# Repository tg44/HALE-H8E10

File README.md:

# HALE H8E10

**H**all ×**8**, **E**ncoder ×**10**. An open-source USB-MIDI pad controller with hall-effect (analog) keys, ten
push-encoders, a small colour display and per-key RGB, built around an
ESP32-S3 so it can also do BLE-MIDI and a Wi-Fi settings page.

Think "LPD8-sized, with velocity and aftertouch that actually come from the
key, and an Ableton/DJ mode flip for the knobs."

> Inspired by the Akai Professional LPD8 and MPK mini. This project is not
> affiliated with or endorsed by Akai; those names are used only to describe
> the layout it takes after.

## What it is

- 8 hall-effect keys (Gateron KS-20 magnetic switches, DRV5055A3 sensors) with
  per-key velocity, aftertouch and rapid-trigger style actuation
- 10 detented push-encoders in two rows; a row reads `[browse][hi][mid][lo][mix]`
  in "DJ" mode and ten macro knobs in "Ableton" mode
- 2.79" 428×142 bar display (NV3007, SPI) in a strip above the keys
- 18 reverse-mount RGB LEDs (SK6812MINI-EA), one per key and one per encoder; no separate status LEDs (the display and ENC1's LED cover status)
- Seeed XIAO ESP32S3 Plus: class-compliant USB-MIDI, BLE-MIDI, Wi-Fi web UI
- Powered from the XIAO's USB-C; no external supply

## Name

The model code follows the Intech/Akai habit of letters-and-counts: `H8E10` is
8 hall-effect keys and 10 encoders, so a 32-key sibling would be `H16E16` and
a fader version `H8E10F4`. **HALE** is the family name (HALl Encoder; also
"hale" as in healthy and strong). Yes, H8 reads as "hate". We're fine with it (or at least I don't _hate_ it, I think its F8 so we can make fun jokes (or F1?)).

## Status

Nothing is ordered yet. The H8E10 schematic and board are drawn and
routed; the case is modelled alongside. Before ordering it, a mini test
board, H4E2 (4 keys, 2 encoders, the same display), checks the footprints
and the hall-sensor circuit. v0 will be a single hand-soldered board. See [docs/plan.md](docs/plan.md) for the order of work and
[docs/decisions.md](docs/decisions.md) for why things are the way they are.

## AI-assisted, not AI-generated

I'm building this to learn electronics, and I use an AI assistant (Claude)
while doing it — as a tutor and a second pair of eyes, not as the designer.
It explains things, suggests parts and helps keep these docs in order. The
schematic and layout are drawn by me in KiCad, every part choice is checked
against its datasheet, and the reasoning is written down in
[docs/decisions.md](docs/decisions.md) so that it can be checked by someone
who knows better.

That's also an invitation: I'm new to this, so if something here is wrong
or naive, an issue saying so is very welcome.

## Repository layout

```
docs/           design notes, decisions, BOM, assembly notes
hardware/H8E10/ KiCad 10 project (schematic, PCB)
hardware/H4E2/  KiCad 10 project of the mini test board
hardware/libs/  project-local symbols, footprints, 3D models
firmware/       Arduino (PlatformIO) firmware for the XIAO ESP32S3
case/           case and plate models (FluidCAD): lib/, h8e10/, mini/
```

## Docs

- [docs/plan.md](docs/plan.md) — order of work: board, case and firmware
  tracks
- [docs/decisions.md](docs/decisions.md) — architecture decisions and the
  reasoning behind them
- [docs/bom.md](docs/bom.md) — bill of materials with LCSC numbers and sources
- [docs/pinout.md](docs/pinout.md) — MCU pin budget and bus assignments
- [docs/layout-references.md](docs/layout-references.md) — key/knob spacing
  and 3D-print thickness references behind `case/lib/parts.js`
- [docs/pcb-notes.md](docs/pcb-notes.md) — layout and assembly rules
- [display candidates](hardware/libs/datasheets/display/candidates.md) — the 2.79" bar (chosen, D16) vs. the
  1.54" ([display.md](hardware/libs/datasheets/display/1.54/display.md)) and others, mechanical

## License

Hardware: CERN-OHL-P-2.0 ([LICENSE-HARDWARE.md](LICENSE-HARDWARE.md)).
Firmware: MIT ([LICENSE](LICENSE)).

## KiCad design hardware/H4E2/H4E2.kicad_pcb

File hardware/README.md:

# Hardware

- `H8E10/` — KiCad 10 project `HALE-H8E10.kicad_pro`, the full board
- `H4E2/` — KiCad 10 project `H4E2.kicad_pro`, the mini test board (D26);
  started as a copy of the H8E10 project
- `libs/` — project-local symbols (`HALE-git.kicad_sym`), footprints
  (`HALE-git.pretty/`), 3D models (`3dmodels/`, sources in its SOURCES.md), datasheets
  (`datasheets/<group>/`: adc, display, encoder, hall, io-expander, led,
  mcu, power, switch). Every
  part used on the board gets all of them here, so the project opens
  without any globally installed library.

Where parts come from:

- LCSC parts: `easyeda2kicad --full --lcsc_id=Cxxxx` gives symbol, footprint
  and 3D model in one go. Check the result against the datasheet.
- switches: marbastlib, ai03 MX_V2
- XIAO: Seeed OPL_Kicad_Library
- display: Cuprum77/kicad-displays

Copy what is used into `libs/`; don't reference the upstream libraries.

See `docs/pcb-notes.md` before placing anything, and `docs/plan.md` for the
order parts are collected and placed in.

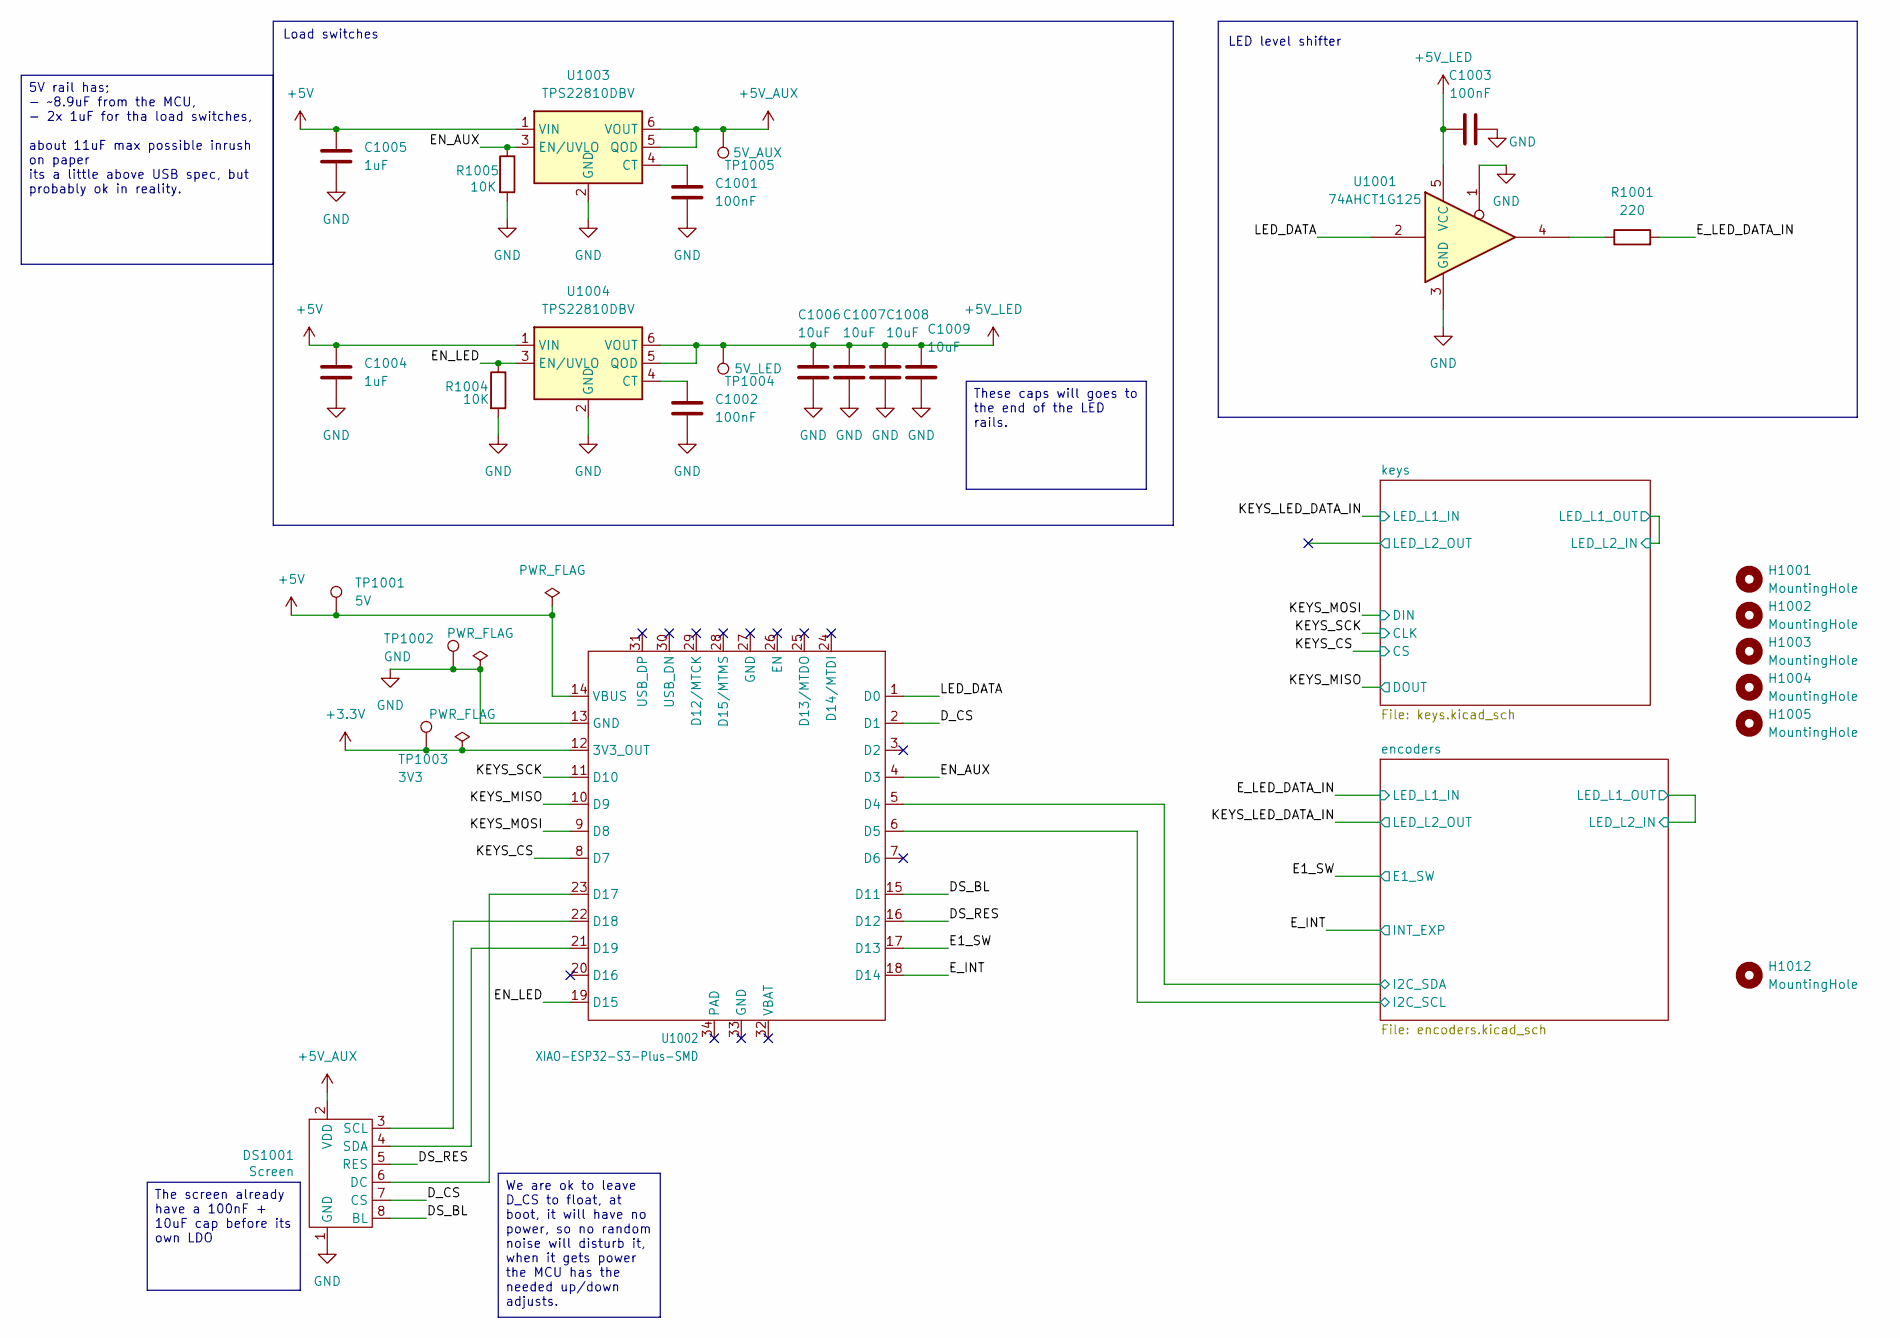
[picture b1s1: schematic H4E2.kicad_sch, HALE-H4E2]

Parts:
C1001, C1002, C1003: 100nF; C_0603_1608Metric_Pad1.08x0.95mm_HandSolder; LCSC C14663
C1004, C1005: 1uF; C_0603_1608Metric_Pad1.08x0.95mm_HandSolder; LCSC C15849
C1006, C1007, C1008, C1009: 10uF; C_0805_2012Metric_Pad1.18x1.45mm_HandSolder; LCSC C15850
DS1001: Screen; Display_2.79_NV3007
H1001, H1002, H1003, H1004, H1005, H1012: MountingHole; MountingHole_2.2mm_M2
R1001: 220; R_0603_1608Metric_Pad0.98x0.95mm_HandSolder; LCSC C22962
R1004, R1005: 10K; R_0603_1608Metric_Pad0.98x0.95mm_HandSolder; LCSC C25804
TP1001: 5V; TestPoint_Pad_D2.0mm
TP1002: GND; TestPoint_Pad_D2.0mm
TP1003: 3V3; TestPoint_Pad_D2.0mm
TP1004: 5V_LED; TestPoint_Pad_D2.0mm
TP1005: 5V_AUX; TestPoint_Pad_D2.0mm
U1001: 74AHCT1G125; SOT-23-5; LCSC C7484
U1002: XIAO-ESP32-S3-Plus-SMD; LCSC C47997983
U1003, U1004: TPS22810DBV; SOT-23-6; LCSC C205990

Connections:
+3.3V: TP1003.1 (1_1), U1002.12 (3V3_OUT); also elsewhere on the board
+5V: C1004.1, C1005.1, TP1001.1 (1_1), U1002.14 (VBUS), U1003.1 (VIN), U1004.1 (VIN)
+5V_AUX: DS1001.2 (VDD), TP1005.1 (1_1), U1003.5 (QOD), U1003.6 (VOUT); also elsewhere on the board
+5V_LED: C1003.2, C1006.1, C1007.1, C1008.1, C1009.1, TP1004.1 (1_1), U1001.5 (VCC), U1004.5 (QOD), U1004.6 (VOUT); also elsewhere on the board
/DS_BL: DS1001.8 (BL), U1002.15 (D11)
/DS_RES: DS1001.5 (RES), U1002.16 (D12)
/D_CS: DS1001.7 (CS), U1002.2 (D1)
/E1_SW: U1002.17 (D13); also elsewhere on the board
/EN_AUX: R1005.1, U1002.4 (D3), U1003.3 (EN/UVLO)
/EN_LED: R1004.1, U1002.19 (D15), U1004.3 (EN/UVLO)
/E_INT: U1002.18 (D14); also elsewhere on the board
/E_LED_DATA_IN: R1001.2; also elsewhere on the board
/KEYS_CS: U1002.8 (D7); also elsewhere on the board
/KEYS_MISO: U1002.10 (D9); also elsewhere on the board
/KEYS_MOSI: U1002.9 (D8); also elsewhere on the board
/KEYS_SCK: U1002.11 (D10); also elsewhere on the board
/LED_DATA: U1001.2, U1002.1 (D0)
/encoders/I2C_SCL: U1002.6 (D5); also elsewhere on the board
/encoders/I2C_SDA: U1002.5 (D4); also elsewhere on the board
GND: C1001.2, C1002.2, C1003.1, C1004.2, C1005.2, C1006.2, C1007.2, C1008.2, C1009.2, DS1001.1 (GND), R1004.2, R1005.2, TP1002.1 (1_1), U1001.1, U1001.3 (GND), U1002.13 (GND), U1003.2 (GND), U1004.2 (GND); also elsewhere on the board
unnamed: DS1001.6 (DC), U1002.23 (D17)
unnamed: DS1001.3 (SCL), U1002.22 (D18)
unnamed: DS1001.4 (SDA), U1002.21 (D19)
unnamed: R1001.1, U1001.4
unnamed: C1001.1, U1003.4 (CT)
unnamed: C1002.1, U1004.4 (CT)

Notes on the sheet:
The screen already have a 100nF + 10uF cap before its own LDO
We are ok to leave D_CS to float, at boot, it will have no power, so no random noise will disturb it, when it gets power the MCU has the needed up/down adjusts.
These caps will goes to the end of the LED rails.
5V rail has; - ~8.9uF from the MCU, - 2x 1uF for tha load switches, about 11uF max possible inrush on paper its a little above USB spec, but probably ok in reality.
Load switches
LED level shifter

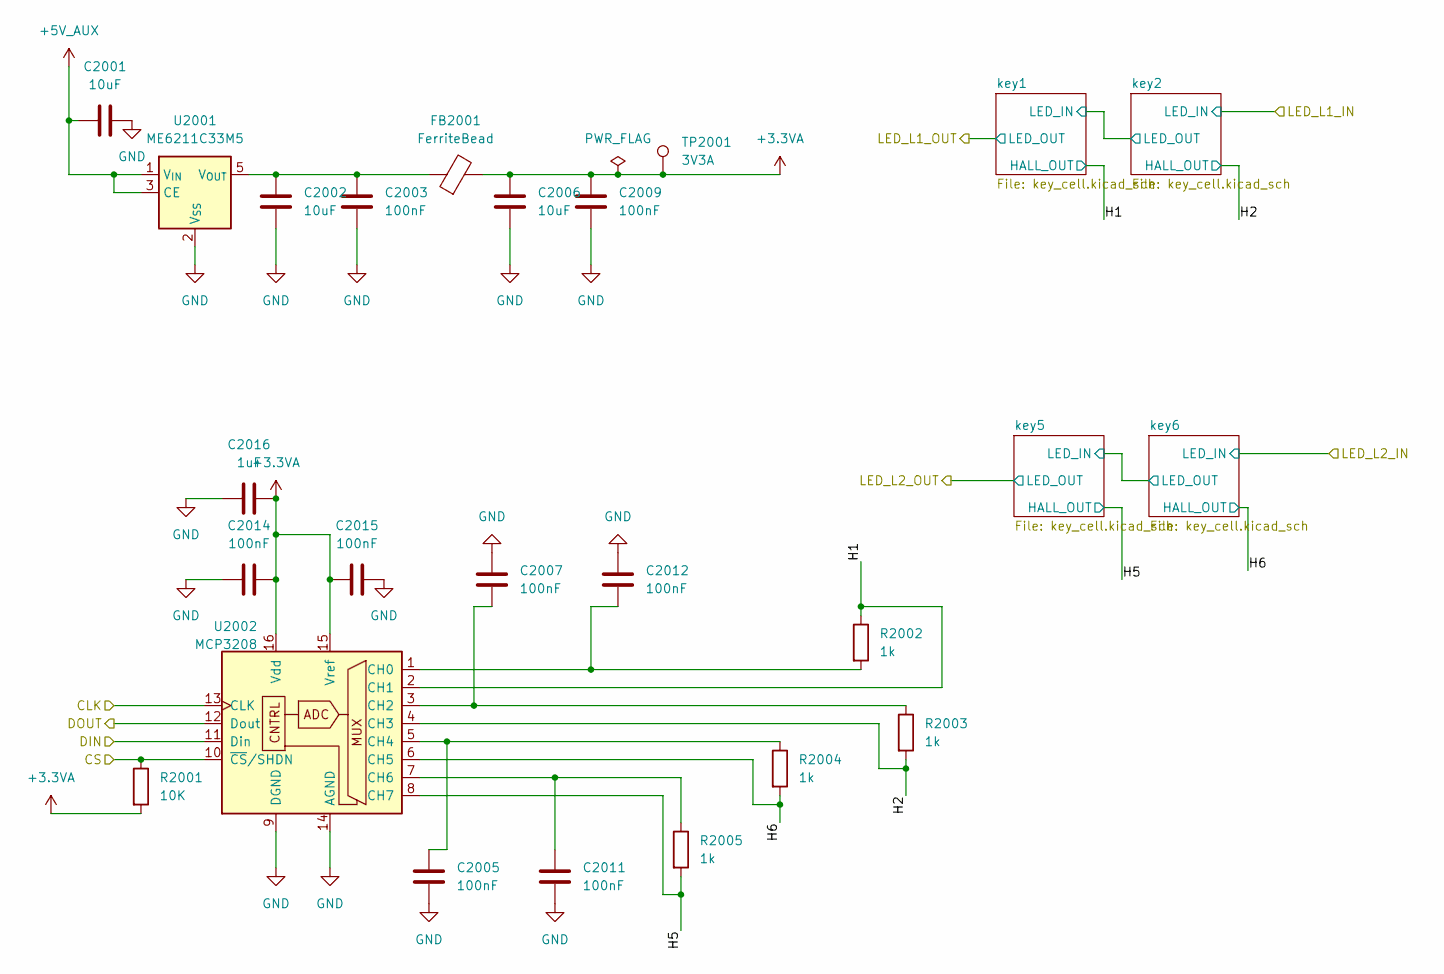
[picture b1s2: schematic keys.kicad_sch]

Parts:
C2001, C2002, C2006: 10uF; C_0805_2012Metric_Pad1.18x1.45mm_HandSolder; LCSC C15850
C2003, C2005, C2007, C2009, C2011, C2012, C2014, C2015: 100nF; C_0603_1608Metric_Pad1.08x0.95mm_HandSolder; LCSC C14663
C2016: 1uF; C_0603_1608Metric_Pad1.08x0.95mm_HandSolder; LCSC C15849
FB2001: FerriteBead; L_0603_1608Metric_Pad1.05x0.95mm_HandSolder; LCSC C1002
R2001: 10K; R_0603_1608Metric_Pad0.98x0.95mm_HandSolder; LCSC C25804
R2002, R2003, R2004, R2005: 1k; R_0603_1608Metric_Pad0.98x0.95mm_HandSolder
TP2001: 3V3A; TestPoint_Pad_D2.0mm
U2001: ME6211C33M5; SOT-23-5; LCSC C82942
U2002: MCP3208; SOIC-16_3.9x9.9mm_P1.27mm; LCSC C626764

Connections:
+3.3VA: C2006.1, C2009.1, C2014.1, C2015.2, C2016.1, FB2001.2, R2001.2, TP2001.1 (1_1), U2002.15 (Vref), U2002.16 (Vdd); also elsewhere on the board
+5V_AUX: C2001.1, U2001.1 (V_{IN}), U2001.3 (CE); also elsewhere on the board
/KEYS_CS: R2001.1, U2002.10 (~CS/SHDN); also elsewhere on the board
/KEYS_MISO: U2002.12 (Dout); also elsewhere on the board
/KEYS_MOSI: U2002.11 (Din); also elsewhere on the board
/KEYS_SCK: U2002.13 (CLK); also elsewhere on the board
/keys/H1: R2002.1, U2002.2 (CH1); also elsewhere on the board
/keys/H2: R2003.2, U2002.4 (CH3); also elsewhere on the board
/keys/H5: R2005.2, U2002.8 (CH7); also elsewhere on the board
/keys/H6: R2004.2, U2002.6 (CH5); also elsewhere on the board
GND: C2001.2, C2002.2, C2003.2, C2005.1, C2006.2, C2007.2, C2009.2, C2011.1, C2012.2, C2014.2, C2015.1, C2016.2, U2001.2 (V_{SS}), U2002.9 (DGND), U2002.14 (AGND); also elsewhere on the board
unnamed: C2002.1, C2003.1, FB2001.1, U2001.5 (V_{OUT})
unnamed: C2012.1, R2002.2, U2002.1 (CH0)
unnamed: C2007.1, R2003.1, U2002.3 (CH2)
unnamed: C2005.2, R2004.1, U2002.5 (CH4)
unnamed: C2011.2, R2005.1, U2002.7 (CH6)

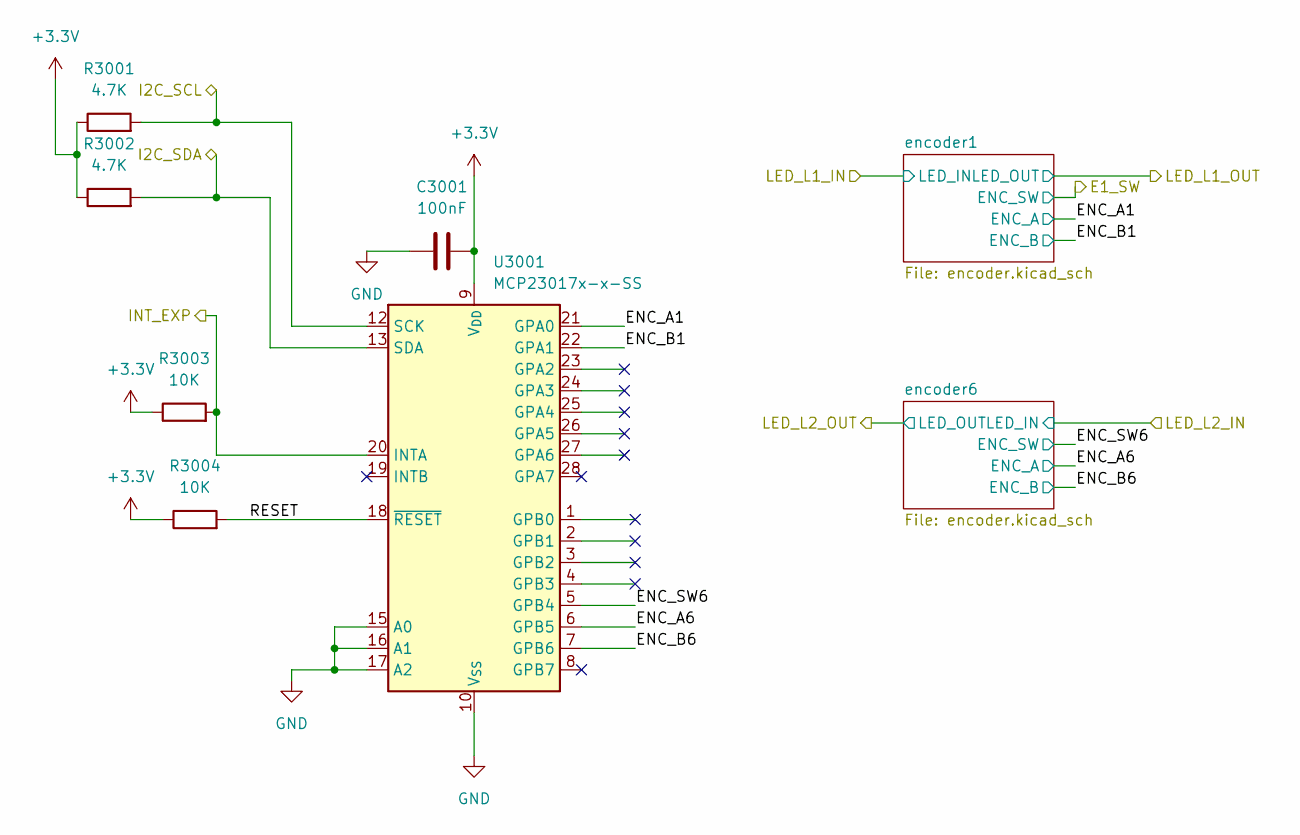
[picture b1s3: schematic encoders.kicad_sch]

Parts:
C3001: 100nF; C_0603_1608Metric_Pad1.08x0.95mm_HandSolder; LCSC C14663
R3001, R3002: 4.7K; R_0603_1608Metric_Pad0.98x0.95mm_HandSolder; LCSC C23162
R3003, R3004: 10K; R_0603_1608Metric_Pad0.98x0.95mm_HandSolder; LCSC C25804
U3001: MCP23017x-x-SS; SSOP-28_5.3x10.2mm_P0.65mm; LCSC C506653

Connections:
+3.3V: C3001.2, R3001.1, R3002.1, R3003.1, R3004.1, U3001.9 (V_{DD}); also elsewhere on the board
/E_INT: R3003.2, U3001.20 (INTA); also elsewhere on the board
/encoders/ENC_A1: U3001.21 (GPA0); also elsewhere on the board
/encoders/ENC_A6: U3001.6 (GPB5); also elsewhere on the board
/encoders/ENC_B1: U3001.22 (GPA1); also elsewhere on the board
/encoders/ENC_B6: U3001.7 (GPB6); also elsewhere on the board
/encoders/ENC_SW6: U3001.5 (GPB4); also elsewhere on the board
/encoders/I2C_SCL: R3001.2, U3001.12 (SCK); also elsewhere on the board
/encoders/I2C_SDA: R3002.2, U3001.13 (SDA); also elsewhere on the board
/encoders/RESET: R3004.2, U3001.18 (~RESET)
GND: C3001.1, U3001.10 (V_{SS}), U3001.15 (A0), U3001.16 (A1), U3001.17 (A2); also elsewhere on the board

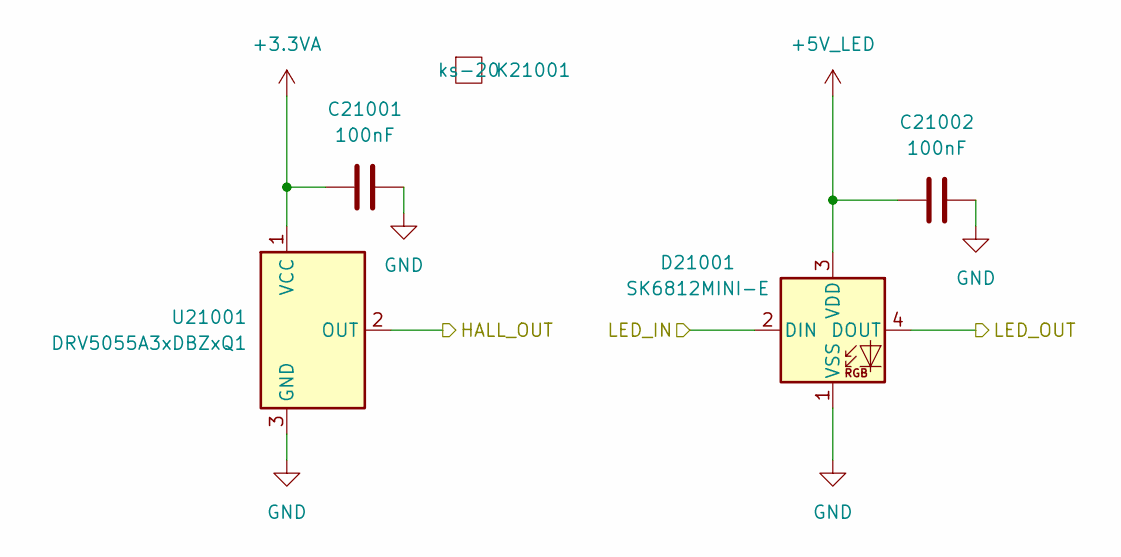
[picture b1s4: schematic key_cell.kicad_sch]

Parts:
C21001, C21002: 100nF; C_0603_1608Metric_Pad1.08x0.95mm_HandSolder; LCSC C14663
D21001: SK6812MINI-E; LED_SK6812MINI-E_3.2x2.8mm_P1.5mm_ReverseMount; LCSC C5149201
K21001: ks-20; Gateron_KS-20
U21001: DRV5055A3xDBZxQ1; SOT-23; LCSC C266128

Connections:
+3.3VA: C21001.1, U21001.1 (VCC); also elsewhere on the board
+5V_LED: C21002.1, D21001.3 (VDD); also elsewhere on the board
/keys/H1: U21001.2 (OUT); also elsewhere on the board
/keys/LED_L1_OUT: D21001.4 (DOUT); also elsewhere on the board
/keys/key1/LED_IN: D21001.2 (DIN); also elsewhere on the board
GND: C21001.2, C21002.2, D21001.1 (VSS), U21001.3 (GND); also elsewhere on the board

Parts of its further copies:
C22001, C22002, C25001, C25002, C26001, C26002: 100nF; C_0603_1608Metric_Pad1.08x0.95mm_HandSolder; LCSC C14663
D22001, D25001, D26001: SK6812MINI-E; LED_SK6812MINI-E_3.2x2.8mm_P1.5mm_ReverseMount; LCSC C5149201
K22001, K25001, K26001: ks-20; Gateron_KS-20
U22001, U25001, U26001: DRV5055A3xDBZxQ1; SOT-23; LCSC C266128

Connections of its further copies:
+3.3VA: C22001.1, C25001.1, C26001.1, U22001.1 (VCC), U25001.1 (VCC), U26001.1 (VCC); also elsewhere on the board
+5V_LED: C22002.1, C25002.1, C26002.1, D22001.3 (VDD), D25001.3 (VDD), D26001.3 (VDD); also elsewhere on the board
/KEYS_LED_DATA_IN: D22001.2 (DIN); also elsewhere on the board
/keys/H2: U22001.2 (OUT); also elsewhere on the board
/keys/H5: U25001.2 (OUT); also elsewhere on the board
/keys/H6: U26001.2 (OUT); also elsewhere on the board
/keys/LED_L1_OUT: D26001.2 (DIN); also elsewhere on the board
/keys/LED_L2_OUT: D25001.4 (DOUT)
/keys/key1/LED_IN: D22001.4 (DOUT); also elsewhere on the board
/keys/key5/LED_IN: D25001.2 (DIN), D26001.4 (DOUT)
GND: C22001.2, C22002.2, C25001.2, C25002.2, C26001.2, C26002.2, D22001.1 (VSS), D25001.1 (VSS), D26001.1 (VSS), U22001.3 (GND), U25001.3 (GND), U26001.3 (GND); also elsewhere on the board

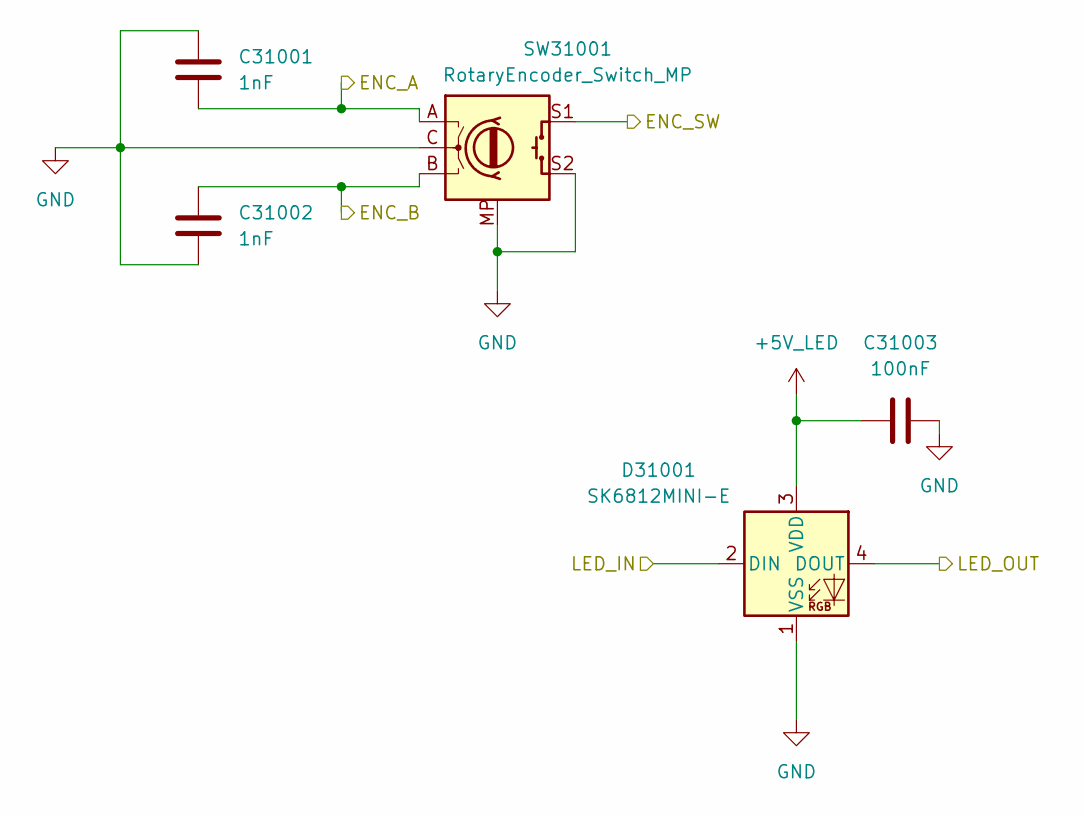
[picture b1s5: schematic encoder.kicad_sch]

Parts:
C31001, C31002: 1nF; C_0603_1608Metric_Pad1.08x0.95mm_HandSolder; LCSC C1588
C31003: 100nF; C_0603_1608Metric_Pad1.08x0.95mm_HandSolder; LCSC C14663
D31001: SK6812MINI-E; LED_SK6812MINI-E_3.2x2.8mm_P1.5mm_ReverseMount; LCSC C5149201
SW31001: RotaryEncoder_Switch_MP; RotaryEncoder_Alps_EC12E-Switch_Vertical_H20mm

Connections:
+5V_LED: C31003.1, D31001.3 (VDD); also elsewhere on the board
/E1_SW: SW31001.S1; also elsewhere on the board
/E_LED_DATA_IN: D31001.2 (DIN); also elsewhere on the board
/encoders/ENC_A1: C31001.2, SW31001.A; also elsewhere on the board
/encoders/ENC_B1: C31002.1, SW31001.B; also elsewhere on the board
/encoders/LED_L1_OUT: D31001.4 (DOUT); also elsewhere on the board
GND: C31001.1, C31002.2, C31003.2, D31001.1 (VSS), SW31001.C, SW31001.MP, SW31001.S2; also elsewhere on the board

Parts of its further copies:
C36001, C36002: 1nF; C_0603_1608Metric_Pad1.08x0.95mm_HandSolder; LCSC C1588
C36003: 100nF; C_0603_1608Metric_Pad1.08x0.95mm_HandSolder; LCSC C14663
D36001: SK6812MINI-E; LED_SK6812MINI-E_3.2x2.8mm_P1.5mm_ReverseMount; LCSC C5149201
SW36001: RotaryEncoder_Switch_MP; RotaryEncoder_Alps_EC12E-Switch_Vertical_H20mm

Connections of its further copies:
+5V_LED: C36003.1, D36001.3 (VDD); also elsewhere on the board
/KEYS_LED_DATA_IN: D36001.4 (DOUT); also elsewhere on the board
/encoders/ENC_A6: C36001.2, SW36001.A; also elsewhere on the board
/encoders/ENC_B6: C36002.1, SW36001.B; also elsewhere on the board
/encoders/ENC_SW6: SW36001.S1; also elsewhere on the board
/encoders/LED_L1_OUT: D36001.2 (DIN); also elsewhere on the board
GND: C36001.1, C36002.2, C36003.2, D36001.1 (VSS), SW36001.C, SW36001.MP, SW36001.S2; also elsewhere on the board

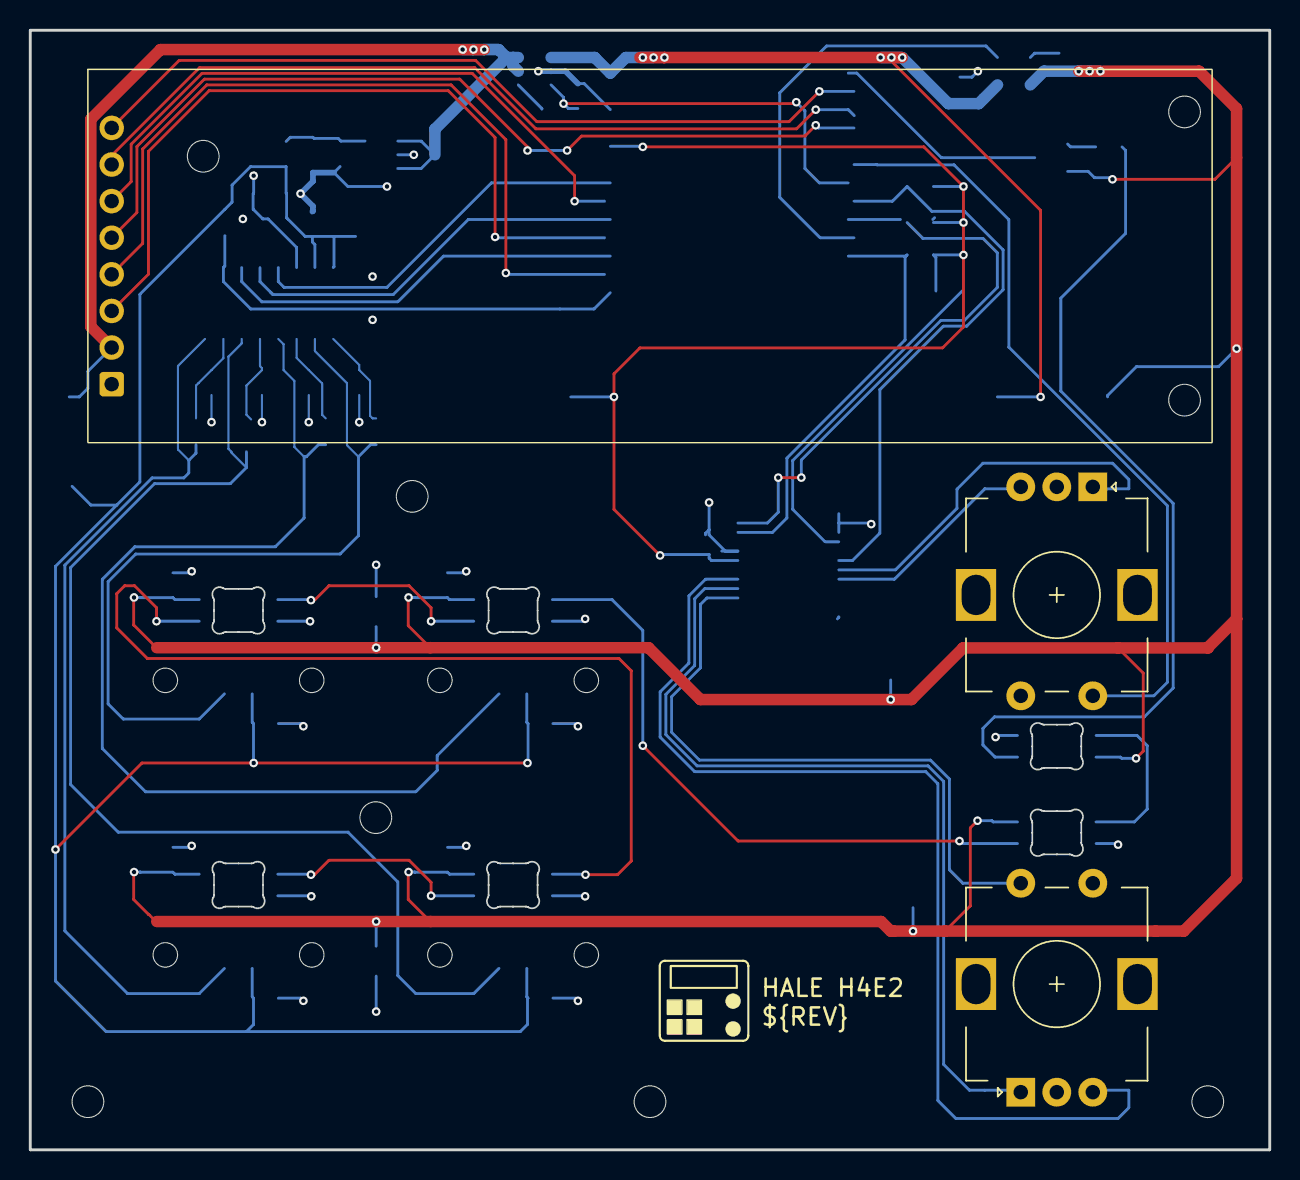
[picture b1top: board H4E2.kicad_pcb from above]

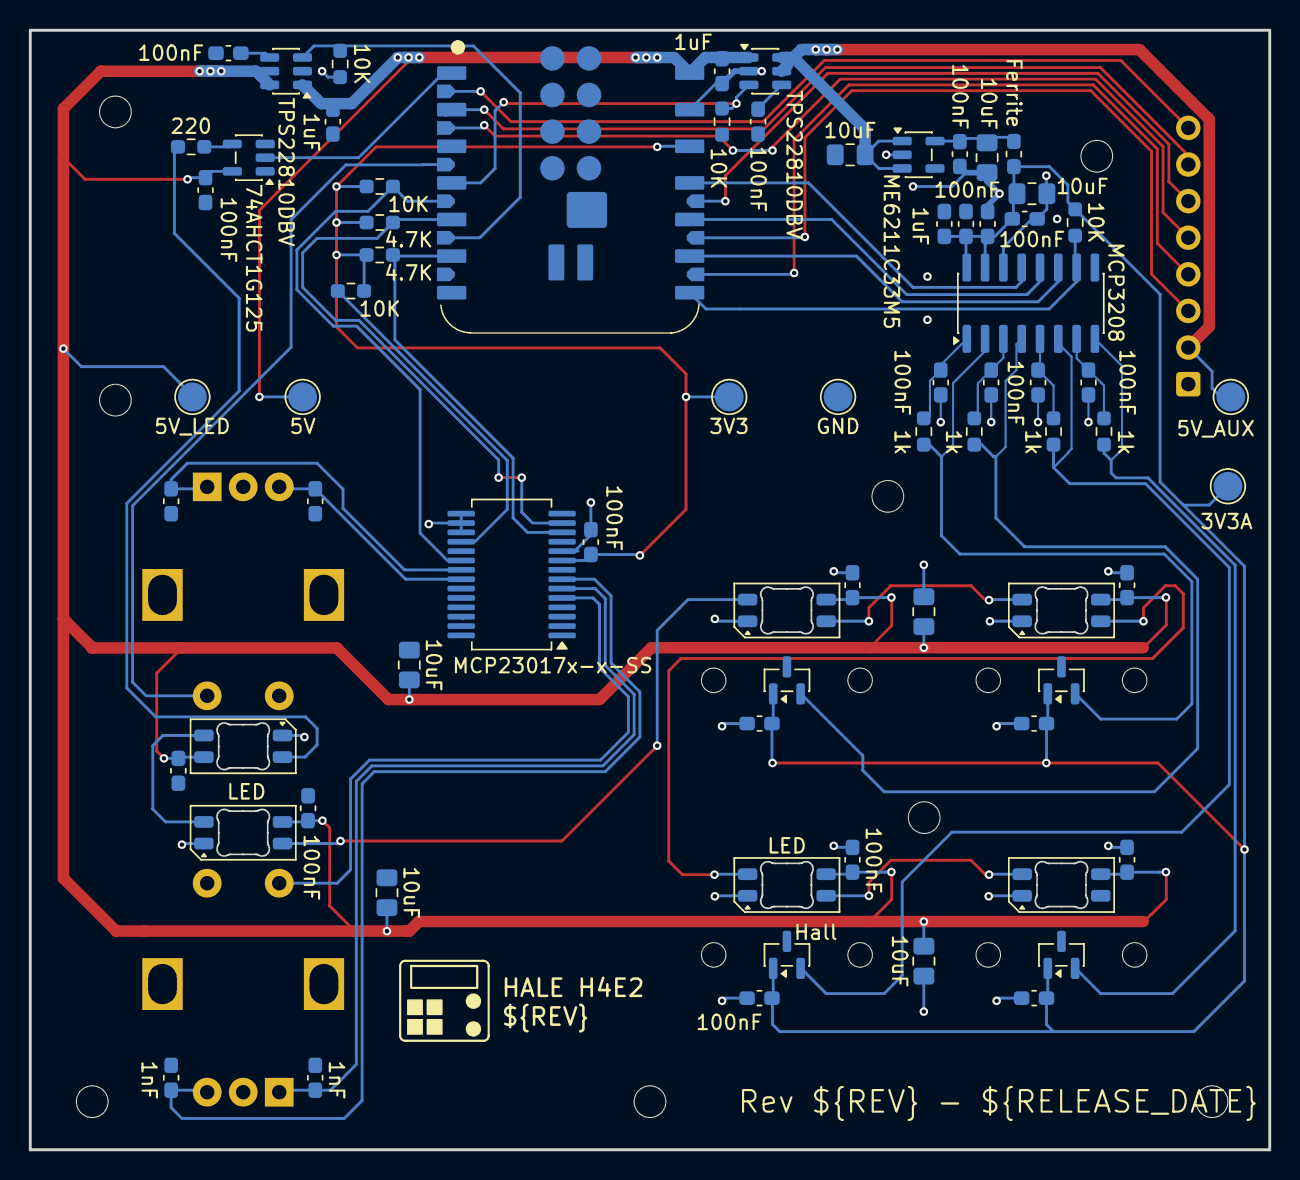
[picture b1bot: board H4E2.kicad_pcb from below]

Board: 2 copper layers, 86.0 x 77.7 mm, 85 parts (74 on the bottom side), 47 nets.
